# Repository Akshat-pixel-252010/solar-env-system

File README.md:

# solar-env-system
Building a real-world environmental sensing system to analyze solar efficiency, sensor reliability, and system optimization under real conditions.

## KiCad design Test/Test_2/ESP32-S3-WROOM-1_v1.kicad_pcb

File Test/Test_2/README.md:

# Solar Environmental System – Prototype 2

## Goal

Develop and validate a low-cost environmental sensing platform capable of collecting reliable environmental data for future solar energy research.

The long-term objective is to study how environmental conditions affect solar panel performance and use the collected data for optimization, prediction, and autonomous energy management research.

---

## Current Stage

Prototype 2 – Hardware Integration & Architecture Validation

Focus Areas:

* PCB validation
* Sensor integration
* Firmware development
* Communication testing
* Data acquisition pipeline
* Failure analysis and debugging

This prototype is intended to identify architectural weaknesses before transitioning to a more reliable STM32-based platform.

---

## Hardware

### Main Controller

* ESP32-S3

### Sensors

* DHT22 (Temperature & Humidity)
* TSL2591 (Light Intensity)
* BMP280 (Pressure & Altitude)
* GPS Module
* MQ135 (Air Quality)
* INA219 
* DS18B20

---

## System Architecture

Current Architecture:

* ESP32-S3
* Custom PCB
* External sensor board
* Breadboard-assisted connections (temporary)

Future Architecture:

* Dedicated STM32 main board
* Dedicated sensor board
* Dedicated power management board
* CAN-FD communication network
* Fully modular design

---

## Dataset

* Environmental measurements
* Sensor validation data
* Prototype testing logs

Dataset :

---

## Development Timeline

### PCB Assembly

* Received Prototype 2 PCB.
* Soldered ESP32-S3 and supporting hardware.
* Began sensor integration.

### Initial Power Failure

Issue:

* Board became extremely hot during power-up.

Investigation:

* Suspected PCB design failure.
* Performed continuity and wiring inspection.

Root Cause:

* VCC and GND were accidentally connected due to soldering/wiring error.

Resolution:

* Isolated affected connection.
* Cut faulty wire connection.
* Removed short circuit.

Lesson Learned:

* Always perform continuity testing between power rails before powering a new PCB.

---

### Wiring Challenges

Issue:

* Large amount of time spent routing and validating connections.

Challenges:

* Correct pin mapping
* Sensor wiring verification
* GPIO reassignment
* UART remapping
* Breadboard integration

Resolution:

* Reassigned multiple GPIOs.
* Verified firmware pin mappings.
* Created working hybrid PCB + breadboard setup.

Lesson Learned:

* Pin mapping documentation should be maintained during development.
* Hybrid prototypes increase debugging complexity.

---

### Sensor Bring-Up

Successfully Tested:

* DHT22
* MQ135

Partially Tested:

* GPS
* TSL2591
* BMP280

Known Issues:

* DS18B20 pull-up resistor incorrectly connected.
* Multiple sensor communication issues still under investigation.

Lesson Learned:

* Sensor-specific electrical requirements must be verified before PCB design freeze.

---

### Firmware Development

Completed:

* Sensor polling framework
* Serial diagnostics
* Pin remapping
* GPS UART configuration
* Sensor testing framework

In Progress:

* WiFi integration
* Firebase integration
* Local dashboard
* Historical data storage

---

### Environmental Failure Event

Issue:

* Rainwater entered exposed electronics.

Effects:

* Temporary VCC-GND conduction.
* Sensor instability.
* Intermittent communication failures.

Resolution:

* Powered system down.
* Dried affected components.
* Re-tested sensors.

Lesson Learned:

* Outdoor electronics require environmental protection before long-term deployment.

---

## Key Engineering Lessons

### Electrical

* Verify power rails before power-up.
* Validate sensor pull-up requirements.
* Include test points on future PCBs.

### Mechanical

* Breadboards are unsuitable for outdoor deployment.
* Temporary wiring increases failure probability.

### Firmware

* Diagnostic tools are critical.
* Sensor-by-sensor validation is more effective than full-system debugging.

### System Design

* Reliability is more important than feature count.
* Architecture validation must occur before research data collection begins.

---

## Current Problems

### Hardware

* Wiring instability
* Breadboard dependency
* Outdoor exposure risks

### Sensors

* Intermittent communication failures
* Invalid readings
* Sensor detection issues

### Environment

* Rain exposure
* Dust accumulation
* Insect interference

---

Research begins once a stable and validated sensing platform is available.

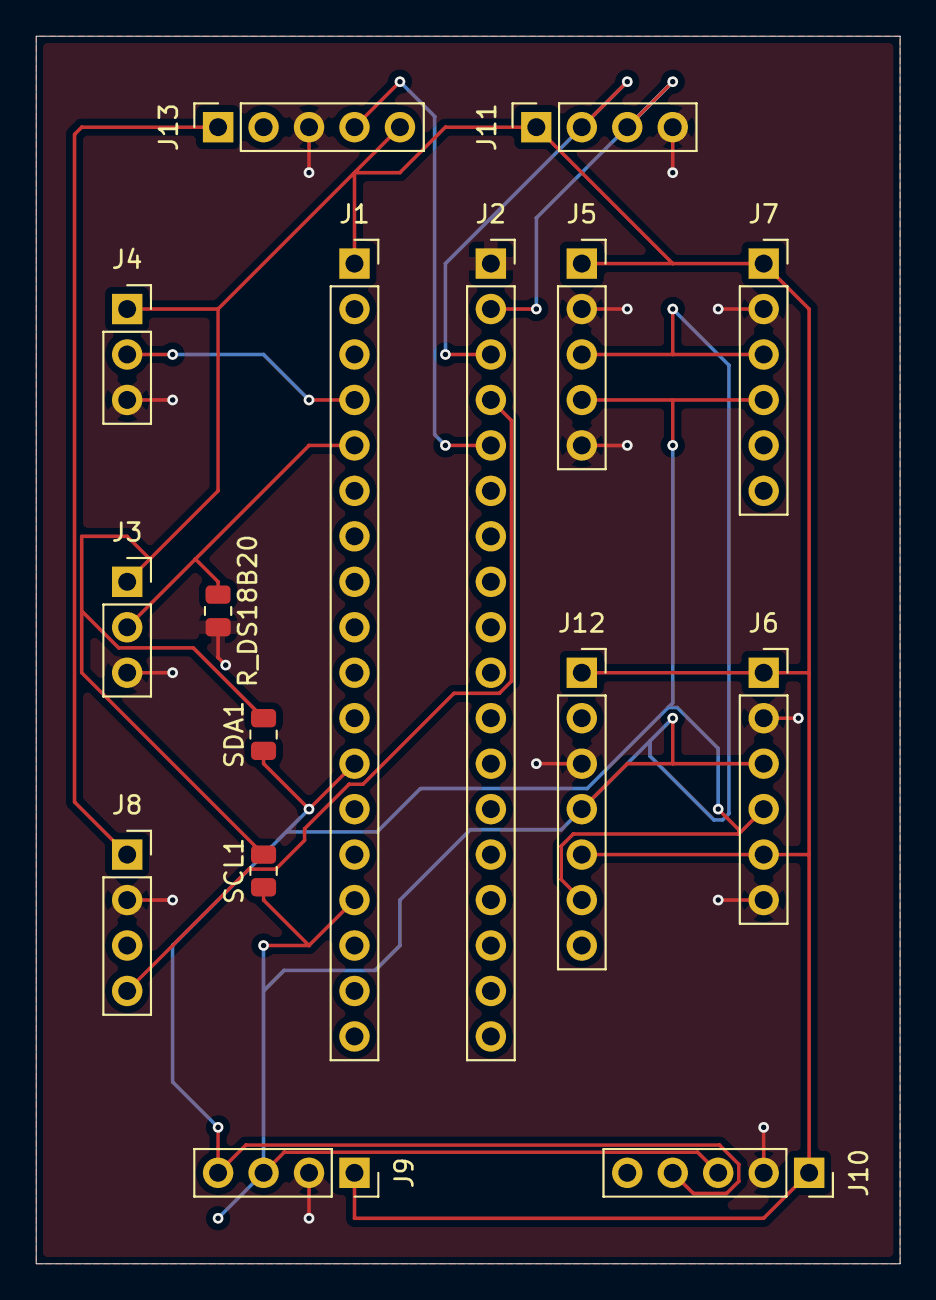
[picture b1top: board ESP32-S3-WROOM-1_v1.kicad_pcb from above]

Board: 2 copper layers, 48.3 x 68.6 mm, 16 parts (0 on the bottom side), 11 nets.

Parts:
J1: ESP_LEFT; PinSocket_1x18_P2.54mm_Vertical
J2: ESP_RIGHT; PinSocket_1x18_P2.54mm_Vertical
J3: DS18B20; PinSocket_1x03_P2.54mm_Vertical
J4: DHT22; PinSocket_1x03_P2.54mm_Vertical
J5: BH175; PinSocket_1x05_P2.54mm_Vertical
J6: BMP280; PinSocket_1x06_P2.54mm_Vertical
J7: INA219; PinSocket_1x06_P2.54mm_Vertical
J8: MQ135; PinSocket_1x04_P2.54mm_Vertical
J9: MLX90614; PinSocket_1x04_P2.54mm_Vertical
J10: TSL25911; PinSocket_1x05_P2.54mm_Vertical
J11: NEO-6M; PinSocket_1x04_P2.54mm_Vertical
J12: BME680; PinSocket_1x07_P2.54mm_Vertical
J13: Ml8511; PinSocket_1x05_P2.54mm_Vertical
R_DS18B20: 4.7k ohm; R_0805_2012Metric
SCL1: 4.7k ohm; R_0805_2012Metric
SDA1: 4.7k ohm; R_0805_2012Metric

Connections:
/1: J2.4 (1), J8.4 (AO)
/2: J2.5 (2), J13.4 (OUT)
/3V3: J1.1 (3V3), J3.1 (+), J4.1 (+), J5.1 (VCC), J6.1 (VCC), J6.5 (CSB), J7.1 (VCC), J9.1 (VCC), J10.1 (VCC), J11.1 (VCC), J12.1 (VIN), J12.5 (SDO), J12.7 (CS), J13.5 (EN), SCL1.2, SDA1.2
/4: J1.4, J4.2 (OUT)
/5: J1.5, J3.2 (DATA), R_DS18B20.1
/5V: J8.1 (VCC), J13.1 (VIN)
/RX: J2.3 (RX), J11.2 (RX)
/SCL: J1.15 (9), J5.3 (SCL), J6.3 (SCL), J7.3 (SCL), J9.3 (SCL), J10.3 (SCL), J12.4 (SCK), SCL1.1
/SDA: J1.12 (8), J5.4 (SDA), J6.4 (SDA), J7.4 (SDA), J9.4 (SDA), J10.4 (SDA), J12.6 (SCI), SDA1.1
/TX: J2.2 (TX), J11.3 (TX)
GND: J2.1 (GND), J3.3 (-), J4.3 (-), J5.2 (GND), J5.5 (ADDR), J6.2 (GND), J6.6 (SDD), J7.2 (GND), J8.2 (GND), J9.2 (GND), J10.2 (GND), J11.4 (GND), J12.3 (GND), J13.3 (GND), R_DS18B20.2

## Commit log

2026-04-25 Create README for Solar Environmental System project
    Added a README file outlining the project's goals, current stage, hardware used, and current problems.
2026-04-26 Update Readme with dataset information
    Added a dataset link to the Readme.
